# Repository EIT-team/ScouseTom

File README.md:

# ScouseTom EIT System
The __ScouseTom__ is versatile Electrical Impedance Tomography (EIT) system. It comprises a commercial current source [Keithley 6221](http://www.tek.com/keithley-low-level-sensitive-and-specialty-instruments/keithley-ultra-sensitive-current-sources-seri) and EEG amplifiers e.g. [Biosemi](http://www.biosemi.com/) or the [actiCHamp](http://www.brainvision.com/actichamp.html0), alongside custom switching/control circuitry and software.

## Making a ScouseTom
If you are interested in making a ScouseTom EIT system, please create an __issue__ in the repo or email us, we would love to help you!

__Checklist__
- [Keithley 6221](http://www.tek.com/keithley-low-level-sensitive-and-specialty-instruments/keithley-ultra-sensitive-current-sources-seri) Current source
- EEG system with sufficient bandwidth. The [Biosemi](http://www.biosemi.com/) and  [actiCHamp](http://www.brainvision.com/actichamp.html0) have been used so far, and likely the [gtec](http://www.gtec.at/) or the [Open-Ephys](http://www.open-ephys.org/) will work too
- Matlab - needed for [processing](https://github.com/EIT-team/Load_data) anyway. Control the system using the Matlab code [here](./src/matlab/)
- [Arduino Due](https://www.arduino.cc/en/Main/arduinoBoardDue) For the controller
- [Arduino Switch Board](./src/schematics/Ard_Shield) This controls the current source and the timing of switching current injection pairs
- [Switch Network](./src/schematics/ScouseTom_SwitchNetwork) At least one, each for 37 channels. This connects the current source to the EEG system and the electrodes

### Citing this work
Please cite the journal article found [here](http://dx.doi.org/10.3390/s17020280)

```
Avery, J., Dowrick, T., Faulkner, M., Goren, N. and Holder, D., 2017.
A Versatile and Reproducible Multi-Frequency Electrical Impedance Tomography System.
Sensors, 17(2), p.280.
```

### Processing the data
To process the data you collect with this system, use the code found in [this repo](https://github.com/EIT-team/Load_data)

### Creating EIT images
Requires a forward model, generated by the code [here](https://github.com/EIT-team/PEITS), and the reconstruction code [here](https://github.com/EIT-team/Reconstruction) to create the images

## Keithley settings
Set on the front panel under `comm`, change `BAUD` to `57.2k` and `Terminator` to `<CR+LF>`

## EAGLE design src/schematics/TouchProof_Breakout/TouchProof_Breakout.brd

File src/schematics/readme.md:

# Schematics
The schematics needed to create a ScouseTom system and custom electrode boards are all here. All files were created in Eaglecad, and the gerber files are also saved. Where relevant, BOM and pick and place data are included.

- __ _Superseded __ - Old files of historical interest
- __Ard Shield__ - Shield for the Arduino Due which controls the ScouseTom System
- __Debug_Phantom__ A simple resistor phantom, used to quickly check the system is functional, as opposed to calibration
- __Dsub_Croc_Connector__ A breakout for a 37-Way Dsub connector to make it easy to solder crocdile clips to it - to connect to tanks etc.
- __Flexible_Electrode_Connector__ Connector blocks for the flexible electrodes used in epicortical studies
- __Mayo_Phantom__ Resistor Phantom matching epicortical voltages, with three switchable impedances. Used to compare hardware for EP studies
- __Parallel_CS__ Simple current source
- __ScouseTom_SwitchNetwork__ Switch network used in ScouseTom system - 37 channels, and can be daisy chained

## The ones you need to  make a ScouseTom System

The two boards you will need are __Ard Shield__ and at least one __ScouseTom_SwitchNetwork__. The [wiki page](https://github.com/EIT-team/ScouseTom/wiki/Building-ScouseTom-Boards) has some useful background for what parts require hand soldering.

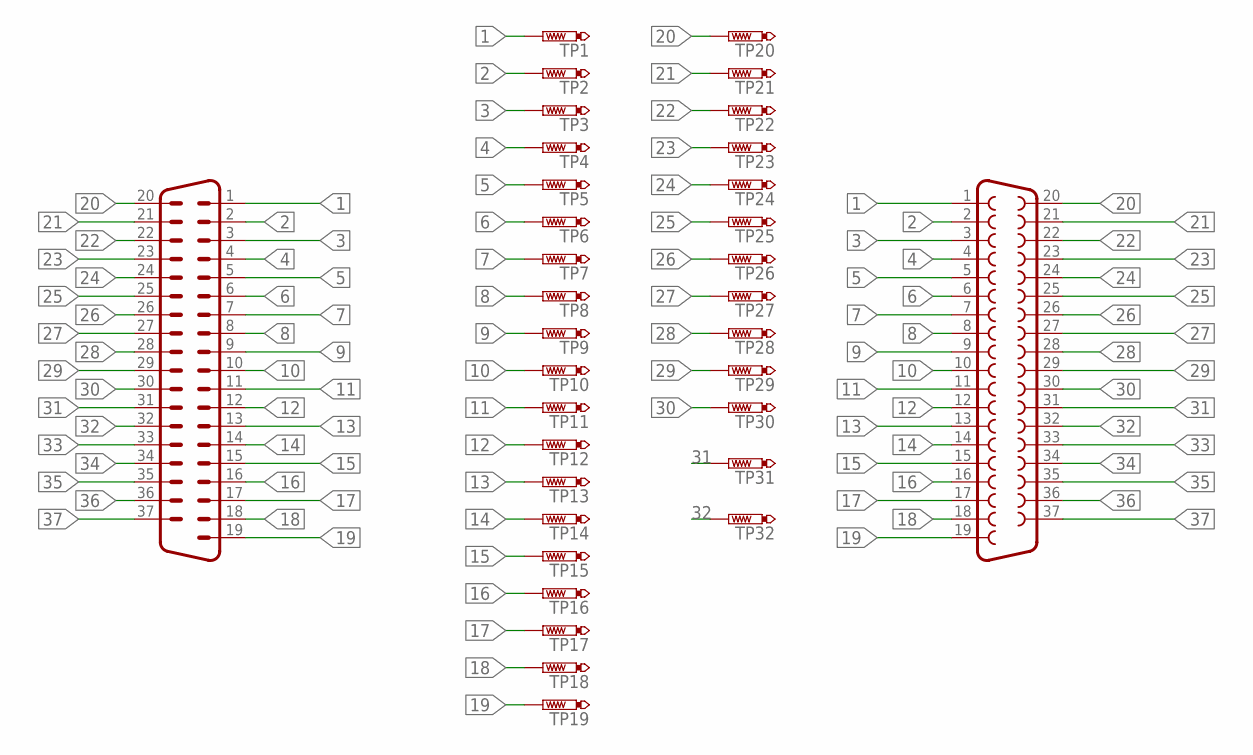
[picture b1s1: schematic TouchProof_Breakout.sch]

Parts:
TP1, TP2, TP3, TP4, TP5, TP6, TP7, TP8, TP9, TP10, TP11, TP12, TP13, TP14, TP15, TP16, TP17, TP18, TP19, TP20, TP21, TP22, TP23, TP24, TP25, TP26, TP27, TP28, TP29, TP30, TP31, TP32: TOUCHPROOF; TOUCHPROOF_PIN
X40: M37HP
X41: F37HP

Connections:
1: TP1.TP, X40.1, X41.1
2: TP2.TP, X40.2, X41.2
3: TP3.TP, X40.3, X41.3
4: TP4.TP, X40.4, X41.4
5: TP5.TP, X40.5, X41.5
6: TP6.TP, X40.6, X41.6
7: TP7.TP, X40.7, X41.7
8: TP8.TP, X40.8, X41.8
9: TP9.TP, X40.9, X41.9
10: TP10.TP, X40.10, X41.10
11: TP11.TP, X40.11, X41.11
12: TP12.TP, X40.12, X41.12
13: TP13.TP, X40.13, X41.13
14: TP14.TP, X40.14, X41.14
15: TP15.TP, X40.15, X41.15
16: TP16.TP, X40.16, X41.16
17: TP17.TP, X40.17, X41.17
18: TP18.TP, X40.18, X41.18
19: TP19.TP, X40.19, X41.19
20: TP20.TP, X40.20, X41.20
21: TP21.TP, X40.21, X41.21
22: TP22.TP, X40.22, X41.22
23: TP23.TP, X40.23, X41.23
24: TP24.TP, X40.24, X41.24
25: TP25.TP, X40.25, X41.25
26: TP26.TP, X40.26, X41.26
27: TP27.TP, X40.27, X41.27
28: TP28.TP, X40.28, X41.28
29: TP29.TP, X40.29, X41.29
30: TP30.TP, X40.30, X41.30
31: TP31.TP, X40.31, X41.31
32: TP32.TP, X40.32, X41.32
33: X40.33, X41.33
34: X40.34, X41.34
35: X40.35, X41.35
36: X40.36, X41.36
37: X40.37, X41.37

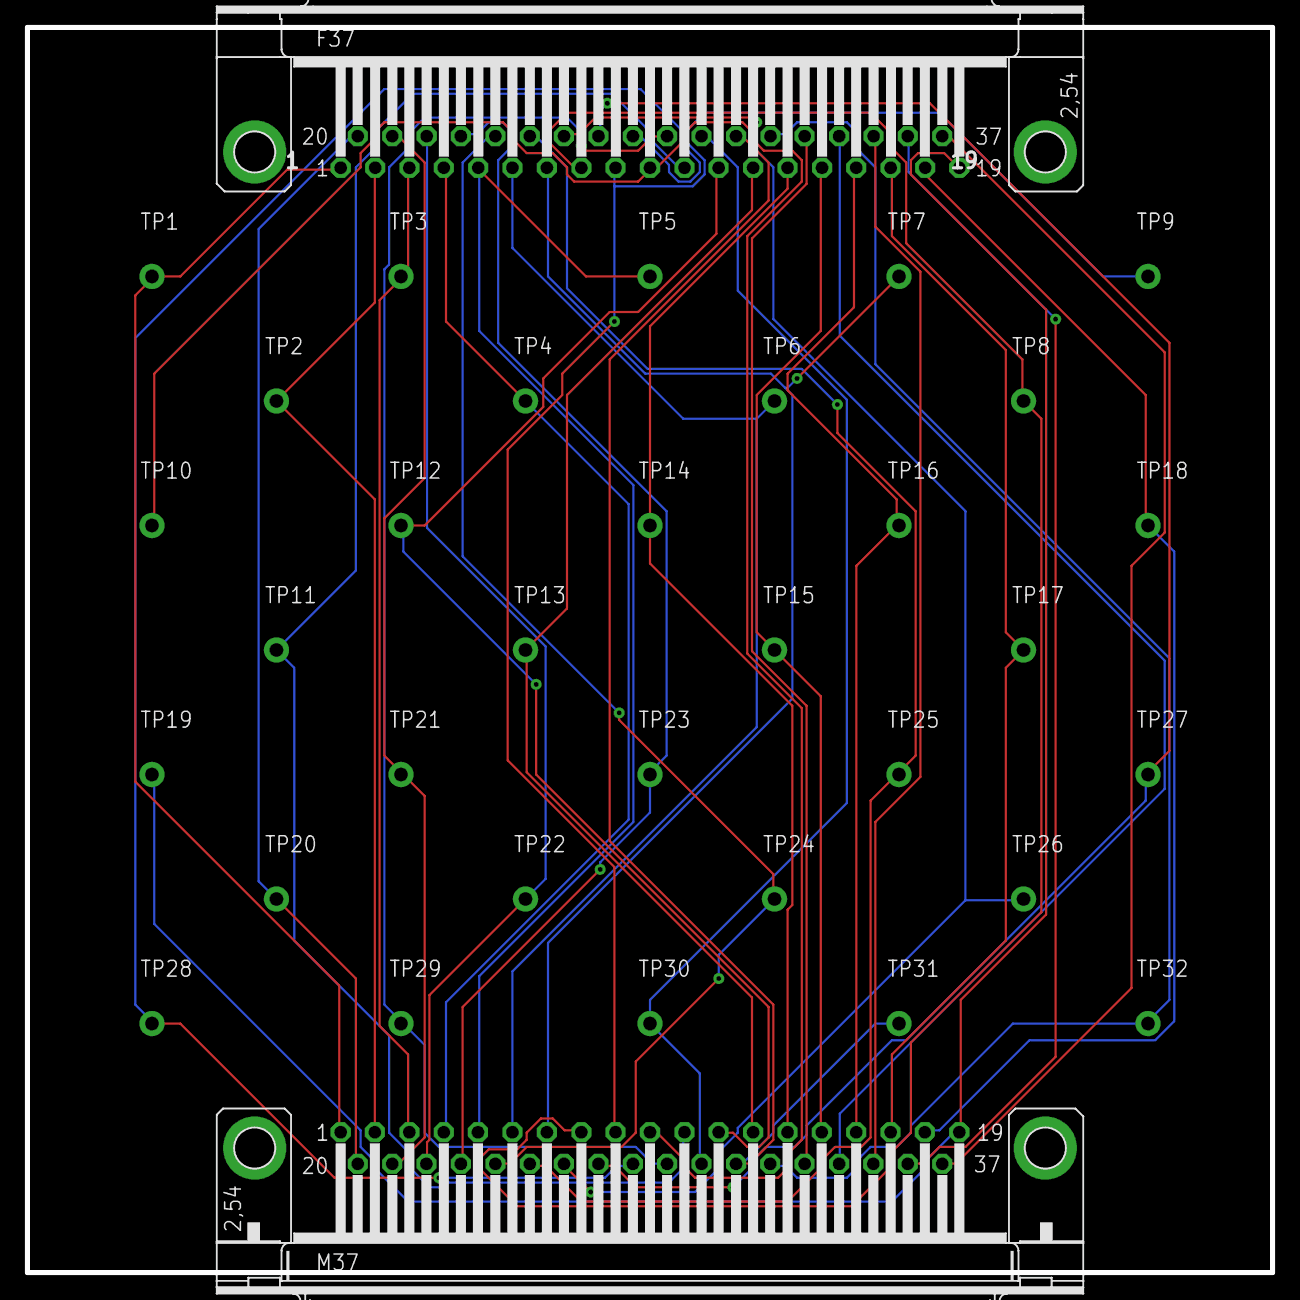
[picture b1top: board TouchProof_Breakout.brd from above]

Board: 2 copper layers, 100.0 x 100.0 mm, 34 parts (0 on the bottom side), 37 nets.

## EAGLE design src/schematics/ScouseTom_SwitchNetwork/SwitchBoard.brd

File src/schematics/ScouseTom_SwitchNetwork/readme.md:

# SwitchBoard

The switchboard connects the source and sink connections of the Keithley 6221 ( the + and - pins) to any two electrodes out of the 37 connections on the DSub.

### Powering the board
The board is powered by a Lipo battery, and a charging circuit is included.

### Daisy Chaining
The control signals to set the switches come from either the `Arduino in` Dsub9, in which case they pass through the Isolators, or the `Daisy Chain in` Dsub9. These are selected by the jumpers labelled `Daisy Chain ON/OFF`

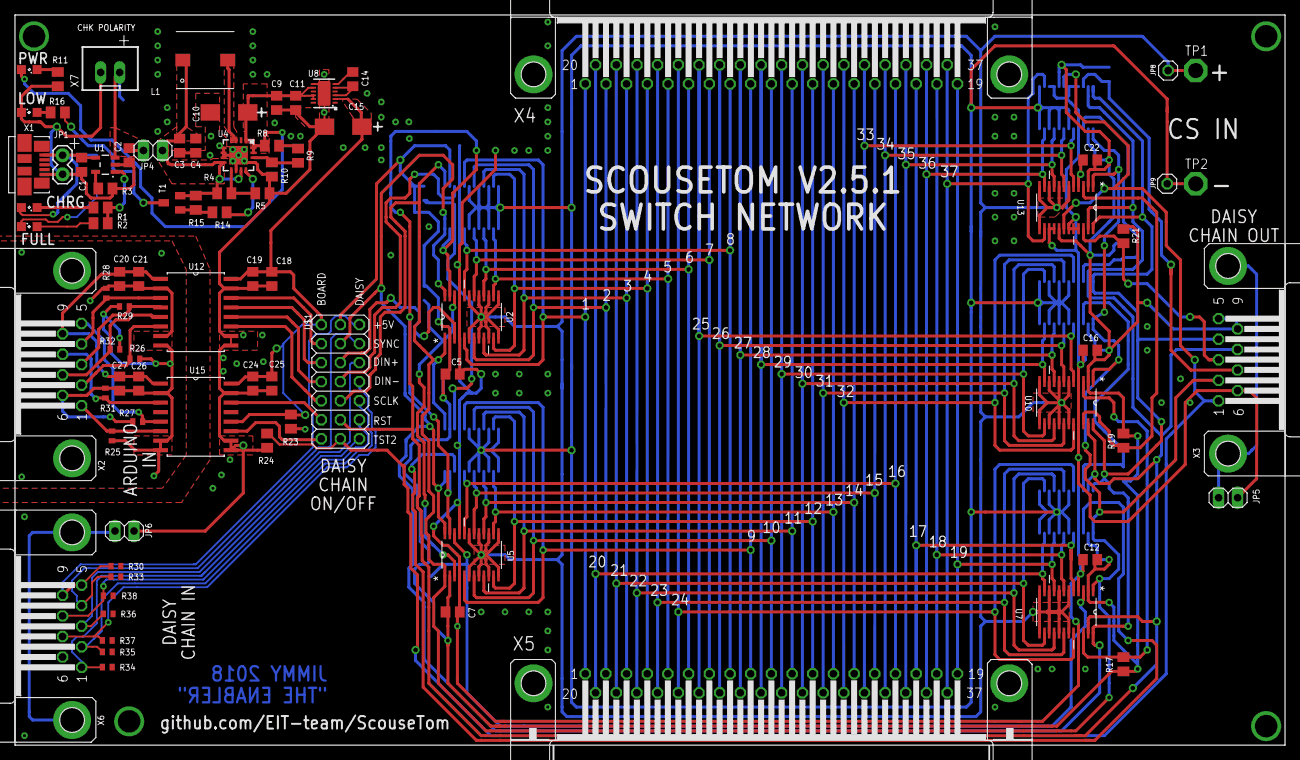
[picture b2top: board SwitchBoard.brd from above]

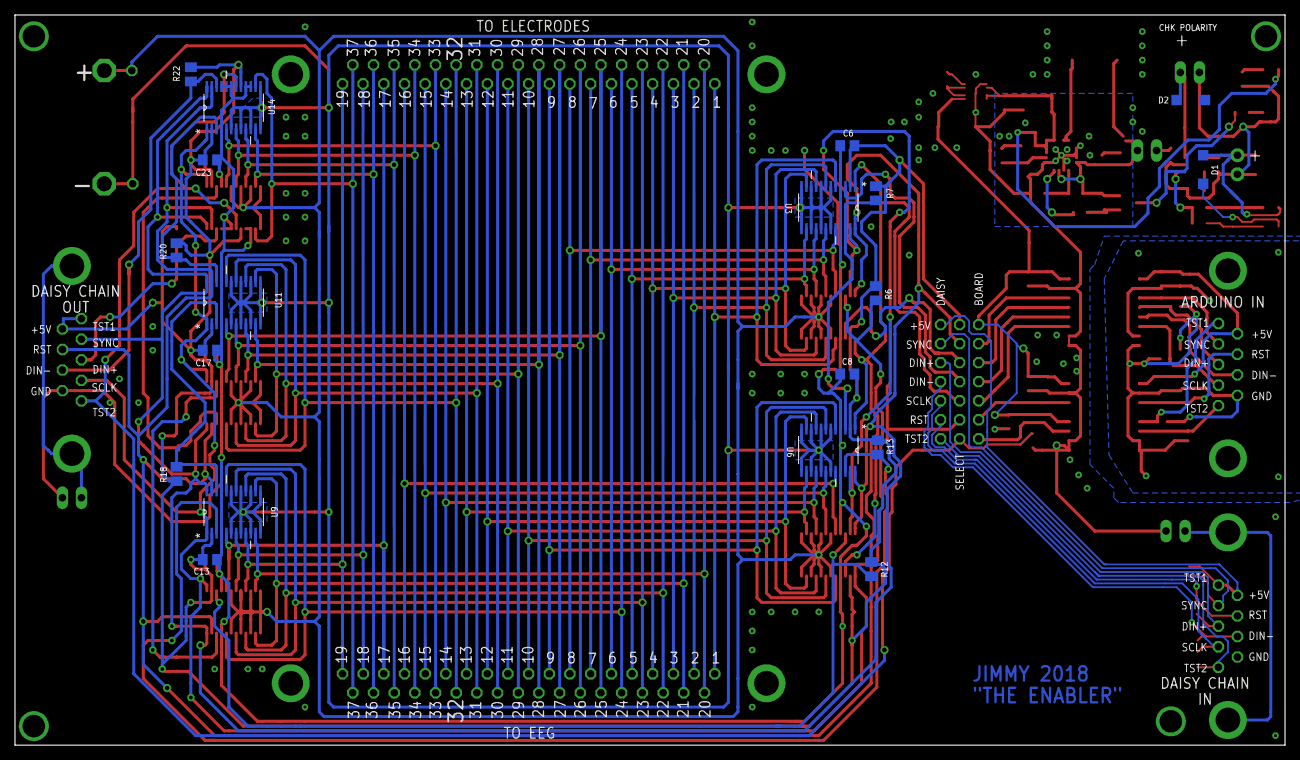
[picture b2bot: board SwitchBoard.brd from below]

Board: 2 copper layers, 169.5 x 97.5 mm, 104 parts (19 on the bottom side), 101 nets.

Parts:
C1, C2, C3, C11: 10uF; C0805
C4, C5, C6, C7, C8, C12, C13, C16, C17, C22, C23: 0.1uF; C0805
C9: 2.2uF; C0805
C10, C15: 100uF; CT6032
C14: 0.01uF; C0805
C18, C20, C24, C26: .1uF; C0805
C19, C21, C25, C27: 1uF; C0805
D1, D2: 1N4148W-7-F; SOD123
JP1: IN; 1X02
JP4: PWR; 1X02
JP5, JP6: Shld; 1X02
JP8: CS_IN+; 1X01
JP9: CS_IN-; 1X01
L1: 6.8uH; WE-PD_7332/7345_PLASTIC_BASE
LED1: YELLOW; SML0805
LED2, LED3: GREEN; SML0805
LED4: RED; SML0805
R1: 470; M0805
R2, R11, R16: 1k; M0805
R3: 2k; M0805
R4: 2M; M0805
R5: 360k; M0805
R6, R7, R12, R13, R17, R18, R19, R20, R21, R22: 10k; M0805
R8: 1.8M; M0805
R9: 82k; M0805
R10: 200k; M0805
R14: 4.7k; M0805
R15: 47k; M0805
R23, R24: 10M; M0805
R25, R26, R27, R28, R29, R30, R31, R32, R33, R34, R35, R36, R37, R38: 10k; R0402
T1: PNP; SOT23-BEC
TP1, TP2: TPPAD1-20; P1-20
U1: MCP73831; SOT23-5
U2, U3, U5, U6, U7, U9, U10, U11, U13, U14: ADG714BRUZ; SOP65P640X120-24N
U4: TPS61090RSAR; QFN16-4X4
U8: LT1763CDE-5; DFN12
U12: ADUM1410ARWZ; SOIC127P1032X265-16N
U15: ADUM1412ARWZ; SOIC127P1032X265-16N
U$1: PINHD-3X7GAP; 3X07
X1: MOLEX_47346-0001
X2: CTR_ARD; F09HP
X3: CTR_OUT; M09HP
X4: DSUB _T; F37HP
X5: DSUB_B; M37HP
X6: CTR_IN; F09HP
X7: JST-XH-02-PIN-LONG-PAD; JST-XH-02-PACKAGE-LONG-PAD

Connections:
5VIN: C1.1, D1.C, JP1.1, LED1.A, U1.4, X1.1
+5V: C20.1, C21.1, C26.1, C27.1, U12.1, U15.1, X2.9
AGND: C1.2, C2.2, C3.2, C4.2, C5.1, C6.1, C7.1, C8.1, C9.2, C10.-, C11.2, C12.1, C13.1, C15.-, C16.1, C17.1, C18.2, C19.2, C22.1, C23.1, C24.2, C25.2, D1.A, D2.A, JP1.2, JP5.1, JP6.2, LED2.C, LED4.C, R3.1, R5.1, R10.1, R11.2, R23.1, R24.1, R30.1, R33.1, R34.1, R35.1, R36.1, R37.1, R38.1, U1.2, U2.4, U2.21, U3.4, U3.21, U4.5, U4.6, U4.7, U4.10, U4.13, U4.EXP, U5.4, U5.21, U6.4, U6.21, U7.4, U7.21, U8.7, U8.EXP, U9.4, U9.21, U10.4, U10.21, U11.4, U11.21, U12.9, U12.10, U12.15, U13.4, U13.15, U13.16, U13.19, U13.20, U13.21, U14.4, U14.15, U14.16, U14.19, U14.20, U14.21, U15.9, U15.10, U15.15, X1.5, X3.6, X6.6, X7.1
CHRG: LED1.C, R1.2
CTR_IN_SHLD: JP6.1, X6.G1, X6.G2
DIN+: U2.3, U$1.17
DIN+2: R6.1, U2.22, U5.3
DIN+3: R12.1, U5.22, U7.3
DIN+4: R17.1, U7.22, U10.3
DIN+5: R19.1, U10.22, U13.3
DIN+_BRD: U12.13, U$1.5
DIN+_DCHN: R36.2, U$1.6, X6.3
DIN+_IN: R29.2, U12.4, X2.3
DIN-: U3.3, U$1.18
DIN-2: R7.1, U3.22, U6.3
DIN-3: R13.1, U6.22, U9.3
DIN-4: R18.1, U9.22, U11.3
DIN-5: R20.1, U11.22, U14.3
DIN-_BRD: U12.12, U$1.7
DIN-_DCHN: R37.2, U$1.8, X6.7
DIN-_IN: R32.2, U12.5, X2.7
DOUT+: R21.1, U13.22, X3.3
DOUT-: R22.1, U14.22, X3.7
GND: C20.2, C21.2, C26.2, C27.2, R25.2, R26.2, R27.1, R28.1, R29.1, R31.1, R32.1, U12.2, U12.7, U12.8, U15.2, U15.7, U15.8, X2.6
IN+: JP8.1, TP1.TP, U2.6, U2.8, U2.10, U2.12, U2.13, U2.15, U2.17, U2.19, U5.6, U5.8, U5.10, U5.12, U5.13, U5.15, U5.17, U5.19, U7.6, U7.8, U7.10, U7.12, U7.13, U7.15, U7.17, U7.19, U10.6, U10.8, U10.10, U10.12, U10.13, U10.15, U10.17, U10.19, U13.6, U13.8, U13.10, U13.12, U13.13
IN-: JP9.1, TP2.TP, U3.6, U3.8, U3.10, U3.12, U3.13, U3.15, U3.17, U3.19, U6.6, U6.8, U6.10, U6.12, U6.13, U6.15, U6.17, U6.19, U9.6, U9.8, U9.10, U9.12, U9.13, U9.15, U9.17, U9.19, U11.6, U11.8, U11.10, U11.12, U11.13, U11.15, U11.17, U11.19, U14.6, U14.8, U14.10, U14.12, U14.13
LBO: R14.1, U4.12
LB_REF: R4.1, R5.2, U4.9
unnamed: C14.1, U8.3, U8.5
unnamed: C14.2, U8.6
unnamed: LED2.A, R2.2
unnamed: R8.1, R9.2
unnamed: LED3.C, R11.1
unnamed: R16.1, T1.C
unnamed: LED4.A, R16.2
unnamed: JP5.2, X3.G1, X3.G2
unnamed: R14.2, R15.1, T1.B
OUT_1: U2.5, U3.5, X4.1, X5.1
OUT_2: U2.7, U3.7, X4.2, X5.2
OUT_3: U2.9, U3.9, X4.3, X5.3
OUT_4: U2.11, U3.11, X4.4, X5.4
OUT_5: U2.14, U3.14, X4.5, X5.5
OUT_6: U2.16, U3.16, X4.6, X5.6
OUT_7: U2.18, U3.18, X4.7, X5.7
OUT_8: U2.20, U3.20, X4.8, X5.8
OUT_9: U5.5, U6.5, X4.9, X5.9
OUT_10: U5.7, U6.7, X4.10, X5.10
OUT_11: U5.9, U6.9, X4.11, X5.11
OUT_12: U5.11, U6.11, X4.12, X5.12
OUT_13: U5.14, U6.14, X4.13, X5.13
OUT_14: U5.16, U6.16, X4.14, X5.14
OUT_15: U5.18, U6.18, X4.15, X5.15
OUT_16: U5.20, U6.20, X4.16, X5.16
OUT_17: U7.5, U9.5, X4.17, X5.17
OUT_18: U7.7, U9.7, X4.18, X5.18
OUT_19: U7.9, U9.9, X4.19, X5.19
OUT_20: U7.11, U9.11, X4.20, X5.20
OUT_21: U7.14, U9.14, X4.21, X5.21
OUT_22: U7.16, U9.16, X4.22, X5.22
OUT_23: U7.18, U9.18, X4.23, X5.23
OUT_24: U7.20, U9.20, X4.24, X5.24
OUT_25: U10.5, U11.5, X4.25, X5.25
OUT_26: U10.7, U11.7, X4.26, X5.26
OUT_27: U10.9, U11.9, X4.27, X5.27
OUT_28: U10.11, U11.11, X4.28, X5.28
OUT_29: U10.14, U11.14, X4.29, X5.29
OUT_30: U10.16, U11.16, X4.30, X5.30
OUT_31: U10.18, U11.18, X4.31, X5.31
OUT_32: U10.20, U11.20, X4.32, X5.32
OUT_33: U13.5, U14.5, X4.33, X5.33
OUT_34: U13.7, U14.7, X4.34, X5.34
OUT_35: U13.9, U14.9, X4.35, X5.35
OUT_36: U13.11, U14.11, X4.36, X5.36
OUT_37: U13.14, U14.14, X4.37, X5.37
PROG: R3.2, U1.5
RESET_IN: R31.2, U15.3, X2.8
SCLK: U2.1, U3.1, U5.1, U6.1, U7.1, U9.1, U10.1, U11.1, U13.1, U14.1, U$1.19, X3.2
SCLK_BRD: U12.11, U$1.9
SCLK_DCHN: R35.2, U$1.10, X6.2
SCLK_IN: R26.1, U12.6, X2.2
STAT: R1.1, R2.1, U1.1
SW: L1.2, U4.3, U4.4
SYNC_IN: R28.2, U12.3, X2.4
TEST_1_IN: R27.2, U15.5, X2.5
TEST_2: R24.2, U13.18, U14.18, U$1.21, X3.1
TEST_2_BRD: U15.11, U$1.13
TEST_2_DCHN: R34.2, U$1.14, X6.1
TEST_2_IN: R25.1, U15.6, X2.1
VBATT_A: C2.1, D2.C, JP4.1, U1.3, X7.2
VBATT_B: C3.1, C4.1, JP4.2, L1.1, R4.2, R15.2, T1.E, U4.8, U4.11
VDD: C5.2, C6.2, C7.2, C8.2, C12.2, C13.2, C16.2, C17.2, C22.2, C23.2, R6.2, R7.2, R12.2, R13.2, R17.2, R18.2, R19.2, R20.2, R21.2, R22.2, U2.2, U3.2, U5.2, U6.2, U7.2, U9.2, U10.2, U11.2, U13.2, U13.17, U14.2, U14.17, U$1.15, X3.5, X3.9
VDD_BRD: C15.+, C18.1, C19.1, C24.1, C25.1, R23.2, U8.2, U12.16, U15.12, U15.16, U$1.1
VDD_DCHN: R30.2, U$1.2, X6.5, X6.9
VREG: C9.1, C10.+, C11.1, LED3.A, R8.2, U4.1, U4.15, U4.16, U8.8, U8.10, U8.11
VSET: R9.1, R10.2, U4.14
~RESET: U2.23, U3.23, U5.23, U6.23, U7.23, U9.23, U10.23, U11.23, U13.23, U14.23, U$1.20, X3.8
~RESET_BRD: U15.14, U$1.11
~RESET_DCHN: R38.2, U$1.12, X6.8
~SYNC: U2.24, U3.24, U5.24, U6.24, U7.24, U9.24, U10.24, U11.24, U13.24, U14.24, U$1.16, X3.4
~SYNC_BRD: U12.14, U$1.3
~SYNC_DCHN: R33.2, U$1.4, X6.4

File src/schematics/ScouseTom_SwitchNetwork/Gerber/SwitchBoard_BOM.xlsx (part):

Part | Value | Device | Package | Description | MPN | OC_FARNELL | PCBTRAIN FREE |  | uniq | cnt non free
C1 | 10uF | C-EUC0805 | C0805 | CAPACITOR, European symbol | MC0805X106K6R3CT | 2320852 |  |  | 2320852 | 4
C2 | 10uF | C-EUC0805 | C0805 | CAPACITOR, European symbol | MC0805X106K6R3CT | 2320852 |  |  | 1759265 | 0
C3 | 10uF | C-EUC0805 | C0805 | CAPACITOR, European symbol | MC0805X106K6R3CT | 2320852 |  |  | 2320829 | 0
C4 | 0.1uF | C-EUC0805 | C0805 | CAPACITOR, European symbol | MC0805B104K500CT | 1759265 | PCB Train Free Component Stock |  | 2353063 | 2
C5 | 0.1uF | C-EUC0805 | C0805 | CAPACITOR, European symbol | MC0805B104K500CT | 1759265 | PCB Train Free Component Stock |  | 1759246 | 0
C6 | 0.1uF | C-EUC0805 | C0805 | CAPACITOR, European symbol | MC0805B104K500CT | 1759265 | PCB Train Free Component Stock |  | 2320827 | 0
C7 | 0.1uF | C-EUC0805 | C0805 | CAPACITOR, European symbol | MC0805B104K500CT | 1759265 | PCB Train Free Component Stock |  | 9492615 | 1
C8 | 0.1uF | C-EUC0805 | C0805 | CAPACITOR, European symbol | MC0805B104K500CT | 1759265 | PCB Train Free Component Stock |  | 1635987 | 1
C9 | 2.2uF | C-EUC0805 | C0805 | CAPACITOR, European symbol | MC0805B225K250CT | 2320829 | PCB Train Free Component Stock |  | 2099243 | 0
C10 | 100uF | CPOL-EUCT6032 | CT6032 | POLARIZED CAPACITOR, European symbol | 293D107X9010C2TE3 | 2353063 |  |  | 2099235 | 0
C11 | 10uF | C-EUC0805 | C0805 | CAPACITOR, European symbol | MC0805X106K6R3CT | 2320852 |  |  | 2099236 | 0
C12 | 0.1uF | C-EUC0805 | C0805 | CAPACITOR, European symbol | MC0805B104K500CT | 1759265 | PCB Train Free Component Stock |  | 2129087 | 0
C13 | 0.1uF | C-EUC0805 | C0805 | CAPACITOR, European symbol | MC0805B104K500CT | 1759265 | PCB Train Free Component Stock |  | 2129113 | 0
C14 | 0.01uF | C-EUC0805 | C0805 | CAPACITOR, European symbol | MC0805B103K500CT | 1759246 | PCB Train Free Component Stock |  | 2129135 | 0
C15 | 100uF | CPOL-EUCT6032 | CT6032 | POLARIZED CAPACITOR, European symbol | 293D107X9010C2TE3 | 2353063 |  |  | 2129375 | 0
C16 | 0.1uF | C-EUC0805 | C0805 | CAPACITOR, European symbol | MC0805B104K500CT | 1759265 | PCB Train Free Component Stock |  | 2129319 | 0
C17 | 0.1uF | C-EUC0805 | C0805 | CAPACITOR, European symbol | MC0805B104K500CT | 1759265 | PCB Train Free Component Stock |  | 9332391 | 0
C18 | .1uF | C-EUC0805 | C0805 | CAPACITOR, European symbol | MC0805B104K500CT | 1759265 | PCB Train Free Component Stock |  | 2129372 | 0
C19 | 1uF | C-EUC0805 | C0805 | CAPACITOR, European symbol | MC0805B105K250CT | 2320827 | PCB Train Free Component Stock |  | 2351393 | 0
C20 | .1uF | C-EUC0805 | C0805 | CAPACITOR, European symbol | MC0805B104K500CT | 1759265 | PCB Train Free Component Stock |  | 2129299 | 0
C21 | 1uF | C-EUC0805 | C0805 | CAPACITOR, European symbol | MC0805B105K250CT | 2320827 | PCB Train Free Component Stock |  | 2129250 | 0
C22 | 0.1uF | C-EUC0805 | C0805 | CAPACITOR, European symbol | MC0805B104K500CT | 1759265 | PCB Train Free Component Stock |  | 2129329 | 0
C23 | 0.1uF | C-EUC0805 | C0805 | CAPACITOR, European symbol | MC0805B104K500CT | 1759265 | PCB Train Free Component Stock |  | 2129417 | 0
C24 | .1uF | C-EUC0805 | C0805 | CAPACITOR, European symbol | MC0805B104K500CT | 1759265 | PCB Train Free Component Stock |  | 2336778 | 0
C25 | 1uF | C-EUC0805 | C0805 | CAPACITOR, European symbol | MC0805B105K250CT | 2320827 | PCB Train Free Component Stock |  | 1332158 | 1
C26 | .1uF | C-EUC0805 | C0805 | CAPACITOR, European symbol | MC0805B104K500CT | 1759265 | PCB Train Free Component Stock |  | 9604367 | 10
C27 | 1uF | C-EUC0805 | C0805 | CAPACITOR, European symbol | MC0805B105K250CT | 2320827 | PCB Train Free Component Stock |  | 1207334 | 1
JP3 | LiPo | M02-JST-2MM-SMT | JST-2-SMD | Header 2 | S2B-PH-SM4-TB(LF)(SN) | 9492615 |  |  | 2115900 | 1
L1 | 6.8uH | WE-PD-7447779006_7332/7345_PLASTIC_BASE | WE-PD_7332/7345_PLASTIC_BASE | SMD-Shielded Power Inductors WE-PD | LT1763CDE-5 | 1635987 |  |  | 2067770 | 1
LED1 | YELLOW | LEDSML0805 | SML0805 | LED | KPT-2012YC | 2099243 | PCB Train Free Component Stock |  | 2377152 | 1
LED2 | GREEN | LEDSML0805 | SML0805 | LED | KPT-2012CGCK | 2099235 | PCB Train Free Component Stock |  | 1568026
LED3 | GREEN | LEDSML0805 | SML0805 | LED | KPT-2012CGCK | 2099235 | PCB Train Free Component Stock |  | #N/A
LED4 | RED | LEDSML0805 | SML0805 | LED | KPT-2012EC | 2099236 | PCB Train Free Component Stock |  | #N/A
R1 | 470 | R-EU_M0805 | M0805 | RESISTOR, European symbol | MC01W08051470R | 2129087 | PCB Train Free Component Stock |  | #N/A
R2 | 1k | R-EU_M0805 | M0805 | RESISTOR, European symbol | MC01W080511K | 2129113 | PCB Train Free Component Stock |  | #N/A
R3 | 2k | R-EU_M0805 | M0805 | RESISTOR, European symbol | MC01W080512K | 2129135 | PCB Train Free Component Stock |  | #N/A
R4 | 2M | R-EU_M0805 | M0805 | RESISTOR, European symbol | MC01W080512M00 | 2129375 | PCB Train Free Component Stock |  | #N/A
R5 | 360k | R-EU_M0805 | M0805 | RESISTOR, European symbol | MC01W08051360K | 2129319 | PCB Train Free Component Stock |  | #N/A
R6 | 10k | R-EU_M0805 | M0805 | RESISTOR, European symbol | MC01W0805110K | 9332391 | PCB Train Free Component Stock |  | #N/A
R7 | 10k | R-EU_M0805 | M0805 | RESISTOR, European symbol | MC01W0805110K | 9332391 | PCB Train Free Component Stock |  | #N/A
R8 | 1.8M | R-EU_M0805 | M0805 | RESISTOR, European symbol | MC01W080511M80 | 2129372 | PCB Train Free Component Stock |  | #N/A
R9 | 82k | R-EU_M0805 | M0805 | RESISTOR, European symbol | MC01W08051820K | 2351393 | PCB Train Free Component Stock |  | #N/A
R10 | 200k | R-EU_M0805 | M0805 | RESISTOR, European symbol | MC01W08051200K | 2129299 | PCB Train Free Component Stock |  | #N/A
R11 | 1k | R-EU_M0805 | M0805 | RESISTOR, European symbol | MC01W080511K | 2129113 | PCB Train Free Component Stock |  | #N/A
R12 | 10k | R-EU_M0805 | M0805 | RESISTOR, European symbol | MC01W0805110K | 9332391 | PCB Train Free Component Stock |  | #N/A
R13 | 10k | R-EU_M0805 | M0805 | RESISTOR, European symbol | MC01W0805110K | 9332391 | PCB Train Free Component Stock |  | #N/A
R14 | 4.7k | R-EU_M0805 | M0805 | RESISTOR, European symbol | MC01W0805147K | 2129250 | PCB Train Free Component Stock |  | #N/A
R15 | 47k | R-EU_M0805 | M0805 | RESISTOR, European symbol | MC01W08051470K | 2129329 | PCB Train Free Component Stock |  | #N/A
R16 | 1k | R-EU_M0805 | M0805 | RESISTOR, European symbol | MC01W080511K | 2129113 | PCB Train Free Component Stock
R17 | 10k | R-EU_M0805 | M0805 | RESISTOR, European symbol | MC01W0805110K | 9332391 | PCB Train Free Component Stock
R18 | 10k | R-EU_M0805 | M0805 | RESISTOR, European symbol | MC01W0805110K | 9332391 | PCB Train Free Component Stock
R19 | 10k | R-EU_M0805 | M0805 | RESISTOR, European symbol | MC01W0805110K | 9332391 | PCB Train Free Component Stock
R20 | 10k | R-EU_M0805 | M0805 | RESISTOR, European symbol | MC01W0805110K | 9332391 | PCB Train Free Component Stock
R21 | 10k | R-EU_M0805 | M0805 | RESISTOR, European symbol | MC01W0805110K | 9332391 | PCB Train Free Component Stock
R22 | 10k | R-EU_M0805 | M0805 | RESISTOR, European symbol | MC01W0805110K | 9332391 | PCB Train Free Component Stock
R23 | 10M | R-EU_M0805 | M0805 | RESISTOR, European symbol | MC01W0805110M0 | 2129417 | PCB Train Free Component Stock
R24 | 10M | R-EU_M0805 | M0805 | RESISTOR, European symbol | MC01W0805110M0 | 2129417 | PCB Train Free Component Stock
T1 | PNP | BC807-40-PNP-SOT23-BEC | SOT23-BEC | PNP Transistror | BC807-40,215 | 2336778 | PCB Train Free Component Stock
U1 | MCP73831 | MCP73831 | SOT23-5 | Miniature single cell, fully integrated Li-Ion, Li-polymer charge management co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 | MCP73831T-2ACI/OT | 1332158
U2 | ADG714BRUZ | ADG714BRUZ | SOP65P640X120-24N | CMOS, Low Voltage Serially Controlled, Octal SPST Switches | ADG714BRUZ | 9604367
U3 | ADG714BRUZ | ADG714BRUZ | SOP65P640X120-24N | CMOS, Low Voltage Serially Controlled, Octal SPST Switches | ADG714BRUZ | 9604367
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
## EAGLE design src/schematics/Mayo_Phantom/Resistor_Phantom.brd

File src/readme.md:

# ScouseTom Source Files
---

## Arduino
Firmware for the Arduino controllers

## Labview
Measurement of stimulator voltage, used in calibration

## Matlab
PC software for controlling the system via USB

## Schematics
Contains all the schematics in Eagle format for the two PCBs - Arduino Shield, and Switch Network. Also contains resistor phantoms, and other misc. phantoms useful in experiments.

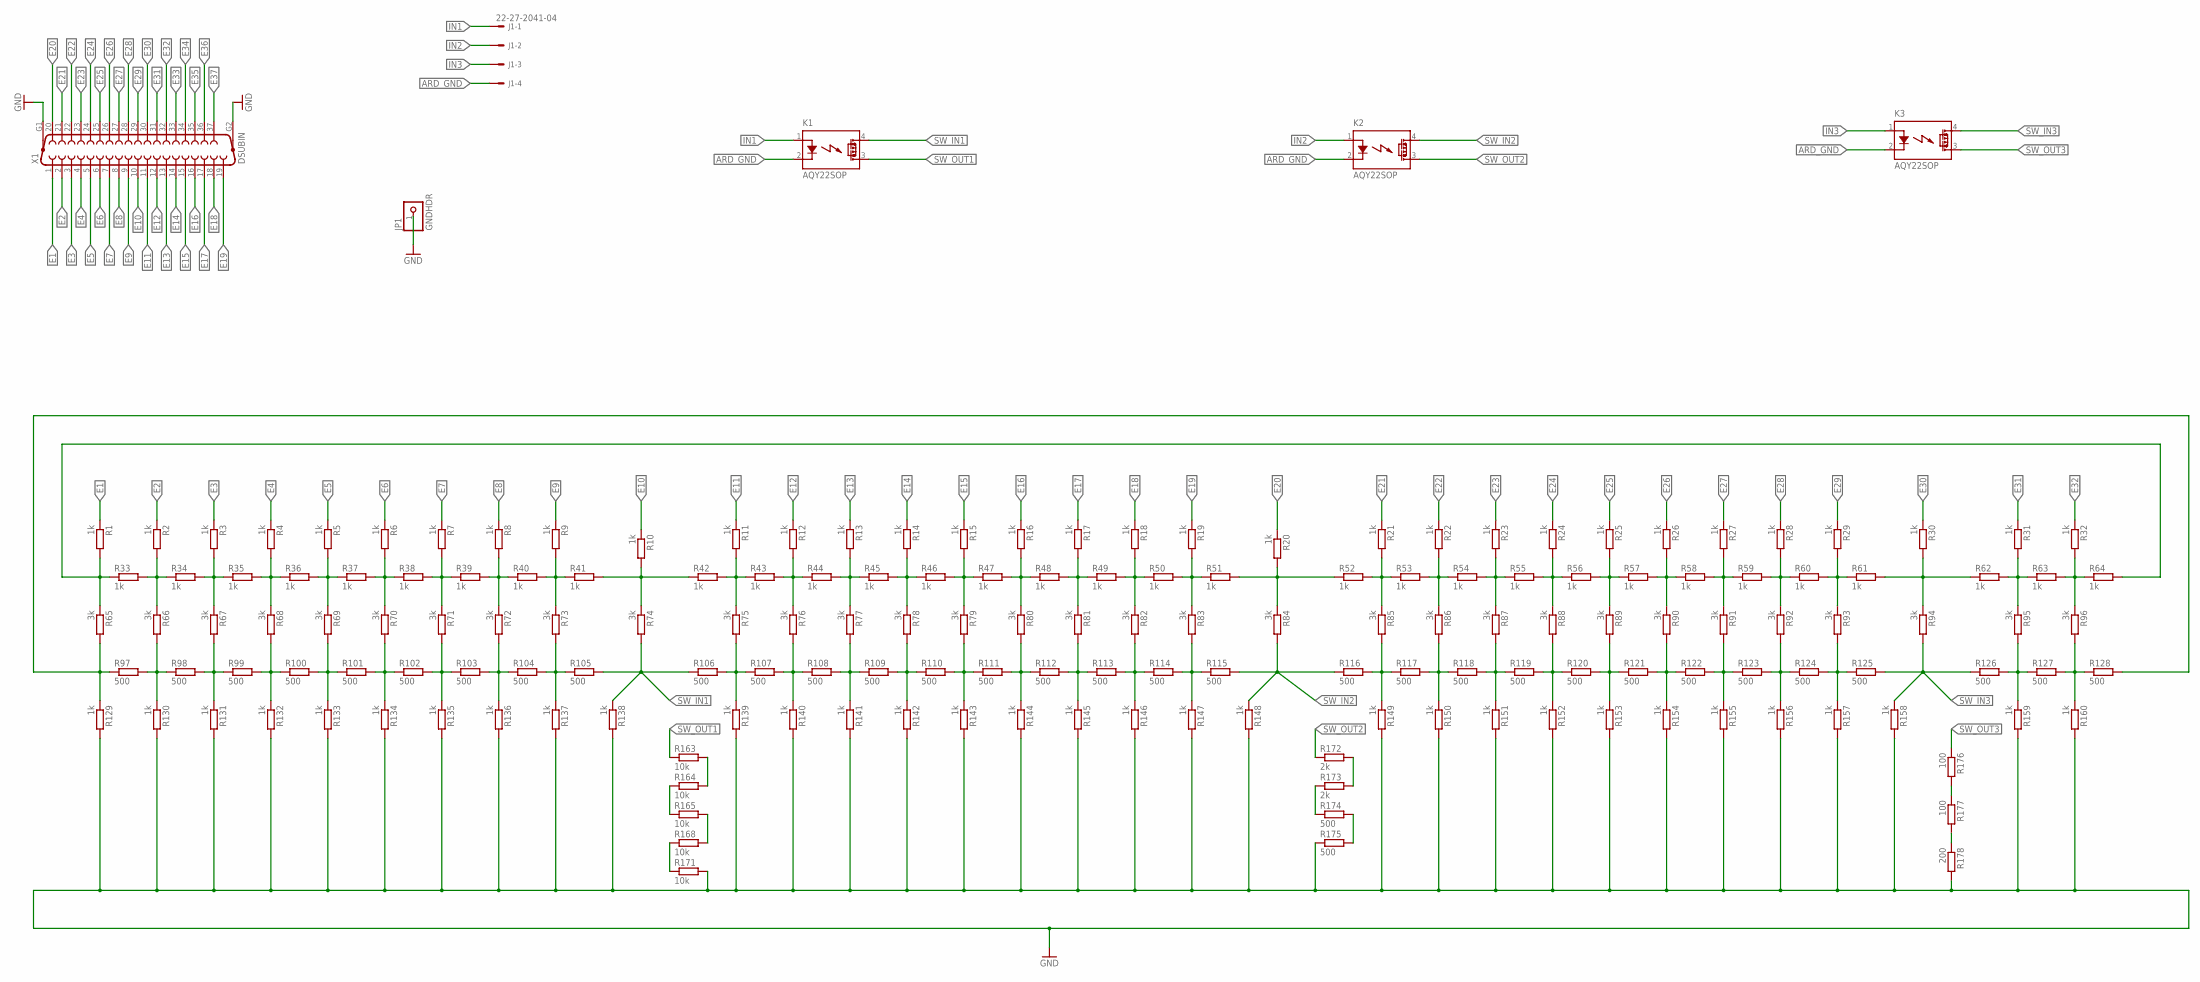
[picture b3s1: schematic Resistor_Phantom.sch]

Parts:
J1: 22-27-2041-04; 6410-04
JP1: GNDHDR; 1X01
K1, K2, K3: AQY22SOP; SOP04
R1, R2, R3, R4, R5, R6, R7, R8, R9, R10, R11, R12, R13, R14, R15, R16, R17, R18, R19, R20, R21, R22, R23, R24, R25, R26, R27, R28, R29, R30, R31, R32, R33, R34, R35, R36, R37, R38, R39, R40, R41, R42, R43, R44, R45, R46, R47, R48, R49, R50, R51, R52, R53, R54, R55, R56, R57, R58, R59, R60, R61, R62, R63, R64, R129, R130, R131, R132, R133, R134, R135, R136, R137, R138, R139, R140, R141, R142, R143, R144, R145, R146, R147, R148, R149, R150, R151, R152, R153, R154, R155, R156, R157, R158, R159, R160: 1k; R0402
R65, R66, R67, R68, R69, R70, R71, R72, R73, R74, R75, R76, R77, R78, R79, R80, R81, R82, R83, R84, R85, R86, R87, R88, R89, R90, R91, R92, R93, R94, R95, R96: 3k; R0402
R97, R98, R99, R100, R101, R102, R103, R104, R105, R106, R107, R108, R109, R110, R111, R112, R113, R114, R115, R116, R117, R118, R119, R120, R121, R122, R123, R124, R125, R126, R127, R128, R174, R175: 500; R0402
R163, R164, R165, R168, R171: 10k; R0402
R172, R173: 2k; R0402
R176, R177: 100; R0402
R178: 200; R0402
X1: DSUBIN; F37VP

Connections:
ARD_GND: J1.4, K1.2 (K), K2.2 (K), K3.2 (K)
E1: R1.1, X1.1
E2: R2.1, X1.2
E3: R3.1, X1.3
E4: R4.1, X1.4
E5: R5.1, X1.5
E6: R6.1, X1.6
E7: R7.1, X1.7
E8: R8.1, X1.8
E9: R9.1, X1.9
E10: R10.1, X1.10
E11: R11.1, X1.11
E12: R12.1, X1.12
E13: R13.1, X1.13
E14: R14.1, X1.14
E15: R15.1, X1.15
E16: R16.1, X1.16
E17: R17.1, X1.17
E18: R18.1, X1.18
E19: R19.1, X1.19
E20: R20.1, X1.20
E21: R21.1, X1.21
E22: R22.1, X1.22
E23: R23.1, X1.23
E24: R24.1, X1.24
E25: R25.1, X1.25
E26: R26.1, X1.26
E27: R27.1, X1.27
E28: R28.1, X1.28
E29: R29.1, X1.29
E30: R30.1, X1.30
E31: R31.1, X1.31
E32: R32.1, X1.32
E33: X1.33
E34: X1.34
E35: X1.35
E36: X1.36
E37: X1.37
E38: R1.2, R33.1, R64.2, R65.1
E39: R2.2, R33.2, R34.1, R66.1
E40: R3.2, R34.2, R35.1, R67.1
E41: R4.2, R35.2, R36.1, R68.1
E42: R5.2, R36.2, R37.1, R69.1
E43: R6.2, R37.2, R38.1, R70.1
E44: R7.2, R38.2, R39.1, R71.1
E45: R8.2, R39.2, R40.1, R72.1
E46: R9.2, R40.2, R41.1, R73.1
E47: R10.2, R41.2, R42.1, R74.1
E48: R11.2, R42.2, R43.1, R75.1
E49: R12.2, R43.2, R44.1, R76.1
E50: R13.2, R44.2, R45.1, R77.1
E51: R14.2, R45.2, R46.1, R78.1
E52: R15.2, R46.2, R47.1, R79.1
E53: R16.2, R47.2, R48.1, R80.1
E54: R17.2, R48.2, R49.1, R81.1
E55: R18.2, R49.2, R50.1, R82.1
E56: R19.2, R50.2, R51.1, R83.1
E57: R20.2, R51.2, R52.1, R84.1
E58: R21.2, R52.2, R53.1, R85.1
E59: R22.2, R53.2, R54.1, R86.1
E60: R23.2, R54.2, R55.1, R87.1
E61: R24.2, R55.2, R56.1, R88.1
E63: R26.2, R57.2, R58.1, R90.1
E64: R27.2, R58.2, R59.1, R91.1
E65: R28.2, R59.2, R60.1, R92.1
E66: R29.2, R60.2, R61.1, R93.1
E67: R30.2, R61.2, R62.1, R94.1
E68: R31.2, R62.2, R63.1, R95.1
E69: R32.2, R63.2, R64.1, R96.1
GND: JP1.1, R129.2, R130.2, R131.2, R132.2, R133.2, R134.2, R135.2, R136.2, R137.2, R138.2, R139.2, R140.2, R141.2, R142.2, R143.2, R144.2, R145.2, R146.2, R147.2, R148.2, R149.2, R150.2, R151.2, R152.2, R153.2, R154.2, R155.2, R156.2, R157.2, R158.2, R159.2, R160.2, R171.2, R175.1, R178.2, X1.G1, X1.G2
IN1: J1.1, K1.1 (A)
IN2: J1.2, K2.1 (A)
IN3: J1.3, K3.1 (A)
unnamed: R25.2, R56.2, R57.1, R89.1
unnamed: R65.2, R97.1, R128.2, R129.1
unnamed: R66.2, R97.2, R98.1, R130.1
unnamed: R67.2, R98.2, R99.1, R131.1
unnamed: R68.2, R99.2, R100.1, R132.1
unnamed: R69.2, R100.2, R101.1, R133.1
unnamed: R70.2, R101.2, R102.1, R134.1
unnamed: R71.2, R102.2, R103.1, R135.1
unnamed: R72.2, R103.2, R104.1, R136.1
unnamed: R73.2, R104.2, R105.1, R137.1
unnamed: R75.2, R106.2, R107.1, R139.1
unnamed: R76.2, R107.2, R108.1, R140.1
unnamed: R77.2, R108.2, R109.1, R141.1
unnamed: R78.2, R109.2, R110.1, R142.1
unnamed: R79.2, R110.2, R111.1, R143.1
unnamed: R80.2, R111.2, R112.1, R144.1
unnamed: R81.2, R112.2, R113.1, R145.1
unnamed: R82.2, R113.2, R114.1, R146.1
unnamed: R83.2, R114.2, R115.1, R147.1
unnamed: R85.2, R116.2, R117.1, R149.1
unnamed: R86.2, R117.2, R118.1, R150.1
unnamed: R87.2, R118.2, R119.1, R151.1
unnamed: R88.2, R119.2, R120.1, R152.1
unnamed: R89.2, R120.2, R121.1, R153.1
unnamed: R90.2, R121.2, R122.1, R154.1
unnamed: R91.2, R122.2, R123.1, R155.1
unnamed: R92.2, R123.2, R124.1, R156.1
unnamed: R93.2, R124.2, R125.1, R157.1
unnamed: R95.2, R126.2, R127.1, R159.1
unnamed: R96.2, R127.2, R128.1, R160.1
unnamed: R163.2, R164.2
unnamed: R164.1, R165.1
unnamed: R165.2, R168.2
unnamed: R168.1, R171.1
unnamed: R172.2, R173.2
unnamed: R173.1, R174.1
unnamed: R174.2, R175.2
unnamed: R176.2, R177.1
unnamed: R177.2, R178.1
SW_IN1: K1.4 (DS1), R74.2, R105.2, R106.1, R138.1
SW_IN2: K2.4 (DS1), R84.2, R115.2, R116.1, R148.1
SW_IN3: K3.4 (DS1), R94.2, R125.2, R126.1, R158.1
SW_OUT1: K1.3 (DS2), R163.1
SW_OUT2: K2.3 (DS2), R172.1
SW_OUT3: K3.3 (DS2), R176.1

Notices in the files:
parts and their libraries:
SparkFun-DiscreteSemi: Licensing: Creative Commons ShareAlike 4.0 International - https://creativecommons.org/licenses/by-sa/4.0
